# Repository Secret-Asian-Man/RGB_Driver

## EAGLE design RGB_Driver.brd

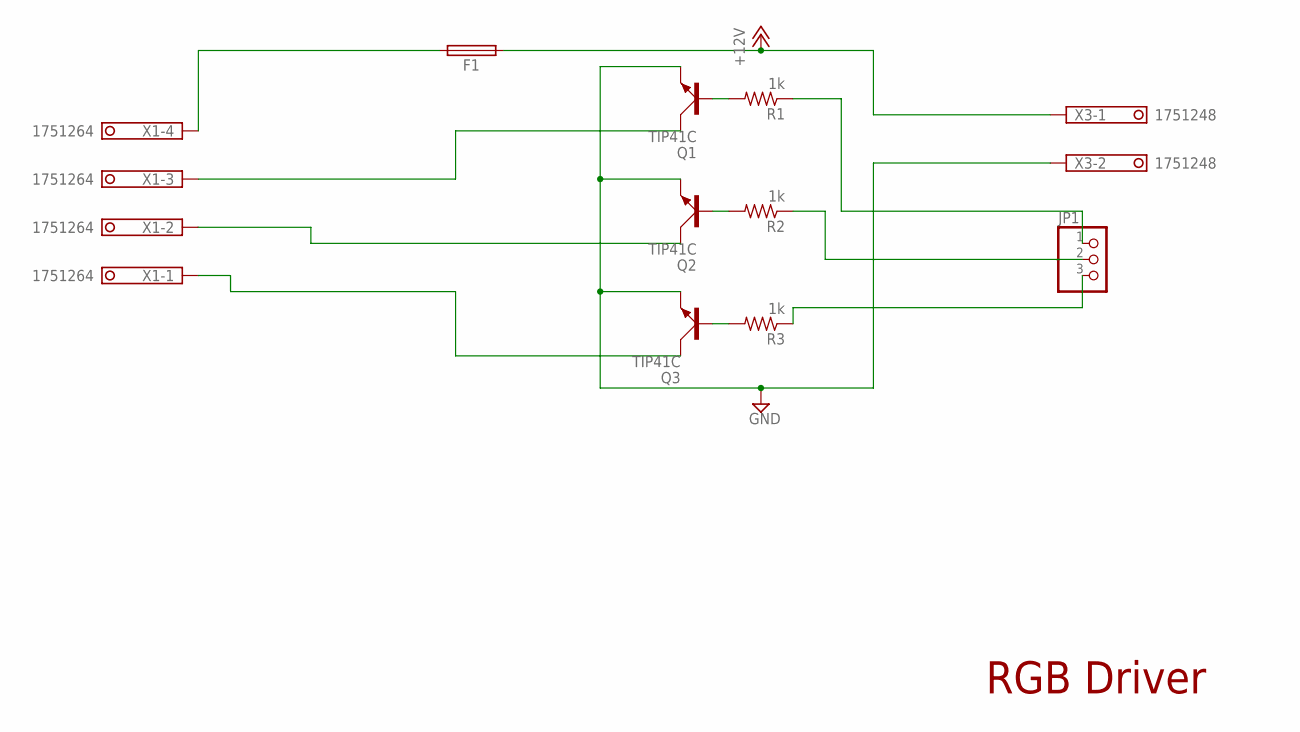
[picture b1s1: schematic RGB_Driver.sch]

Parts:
F1: SHK20L
JP1: PINHD-1X3; 1X03
Q1, Q2, Q3: TIP41C; TO220AV
R1, R2, R3: 1k; 0204/7
X1: 1751264
X3: 1751248

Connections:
+12V: F1.1A, X3.1
GND: Q1.E, Q2.E, Q3.E, X3.2
unnamed: Q1.B, R1.2
unnamed: Q2.B, R2.2
unnamed: Q3.B, R3.2
unnamed: Q1.C, X1.3
unnamed: Q2.C, X1.2
unnamed: Q3.C, X1.1
unnamed: JP1.3, R3.1
unnamed: JP1.2, R2.1
unnamed: JP1.1, R1.1
unnamed: F1.2A, X1.4

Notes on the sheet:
RGB Driver

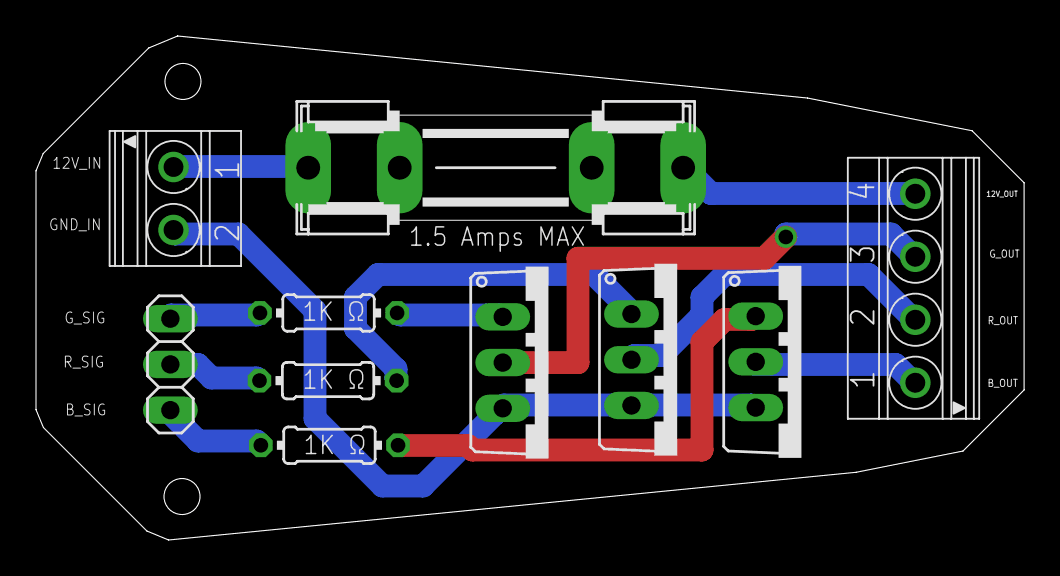
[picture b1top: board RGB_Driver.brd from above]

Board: 2 copper layers, 54.9 x 28.0 mm, 10 parts (0 on the bottom side), 12 nets.

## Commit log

2019-05-08 Initial upload
2019-05-16 Add files via upload
    - Add header pins
    - Add fuse
    - Add 2 slot terminal block
    - Remove 5 slot terminal block
